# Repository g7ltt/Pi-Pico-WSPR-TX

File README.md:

# Pi-Pico-WSPR-TX
17M WSPR transmitter for the Pi Pico (other bands possible with filter changes)

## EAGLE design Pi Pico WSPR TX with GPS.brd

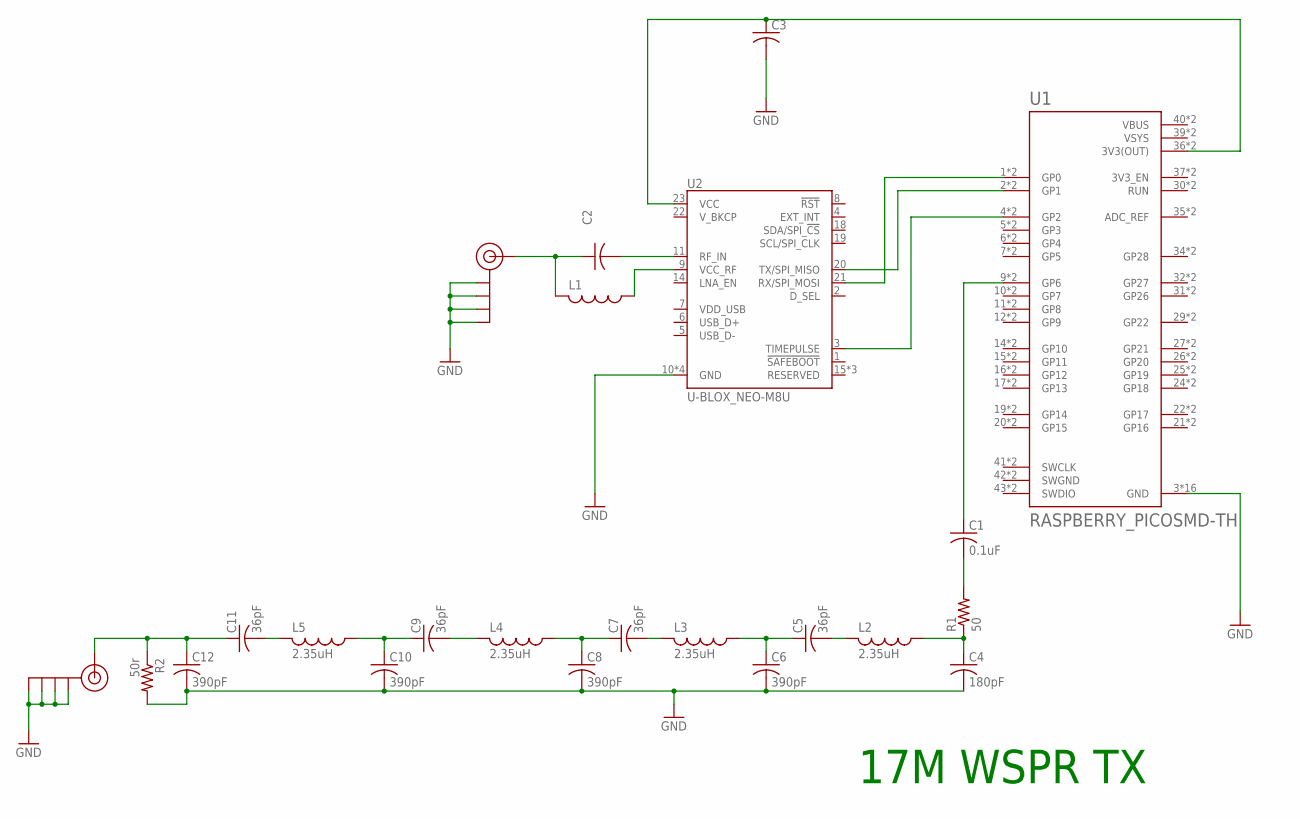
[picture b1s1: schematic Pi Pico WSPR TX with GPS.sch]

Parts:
C1: 0.1uF; C0603
C2, C3: C-USC0603; C0603
C4: 180pF; C0603
C5, C7, C9, C11: 36pF; C0603
C6, C8, C10, C12: 390pF; C0603
J$1, J$2: SMA_EDGE; SMA-EDGE
L1: L-USL2012C; L2012C
L2, L3, L4, L5: 2.35uH; L2012C
R1: 50; R0603
R2: 50r; R0603
U1: RASPBERRY_PICOSMD-TH; PICO-PKG
U2: U-BLOX_NEO-M8U; NEO-M9N/M8T/M8U/D9S/F9P

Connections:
GND: C3.2, C4.2, C6.2, C8.2, C10.2, C12.2, J$1.GND@0 (GND), J$1.GND@1 (GND), J$1.GND@2 (GND), J$1.GND@3 (GND), J$2.GND@0 (GND), J$2.GND@1 (GND), J$2.GND@2 (GND), J$2.GND@3 (GND), R2.2, U1.3 (GND), U1.8 (GND), U1.13 (GND), U1.18 (GND), U1.23 (GND), U1.28 (GND), U1.33 (GND), U1.38 (GND), U1.P$3 (GND), U1.P$8 (GND), U1.P$13 (GND), U1.P$18 (GND), U1.P$23 (GND), U1.P$28 (GND), U1.P$33 (GND), U1.P$38 (GND), U2.10 (GND), U2.12 (GND), U2.13 (GND), U2.24 (GND)
unnamed: C2.1, J$1.SIG (SIGNAL), L1.2
unnamed: C3.1, U1.36 (3V3(OUT)), U1.P$36 (3V3(OUT)), U2.23 (VCC)
unnamed: U1.4 (GP2), U1.P$4 (GP2), U2.3 (TIMEPULSE)
unnamed: C1.1, U1.9 (GP6), U1.P$9 (GP6)
unnamed: U1.1 (GP0), U1.P$1 (GP0), U2.21 (RX/SPI_MOSI)
unnamed: U1.2 (GP1), U1.P$2 (GP1), U2.20 (TX/SPI_MISO)
unnamed: C1.2, R1.2
unnamed: C2.2, U2.11 (RF_IN)
unnamed: L1.1, U2.9 (VCC_RF)
unnamed: C11.2, L5.2
unnamed: C4.1, L2.1, R1.1
unnamed: C5.2, L2.2
unnamed: C5.1, C6.1, L3.1
unnamed: C7.2, L3.2
unnamed: C7.1, C8.1, L4.1
unnamed: C9.2, L4.2
unnamed: C9.1, C10.1, L5.1
unnamed: C11.1, C12.1, J$2.SIG (SIGNAL), R2.1
SWGND: U1.42 (SWGND), U1.P$42 (SWGND)
VBUS: U1.40 (VBUS), U1.P$40 (VBUS)
VSYS: U1.39 (VSYS), U1.P$39 (VSYS)

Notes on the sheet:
17M WSPR TX

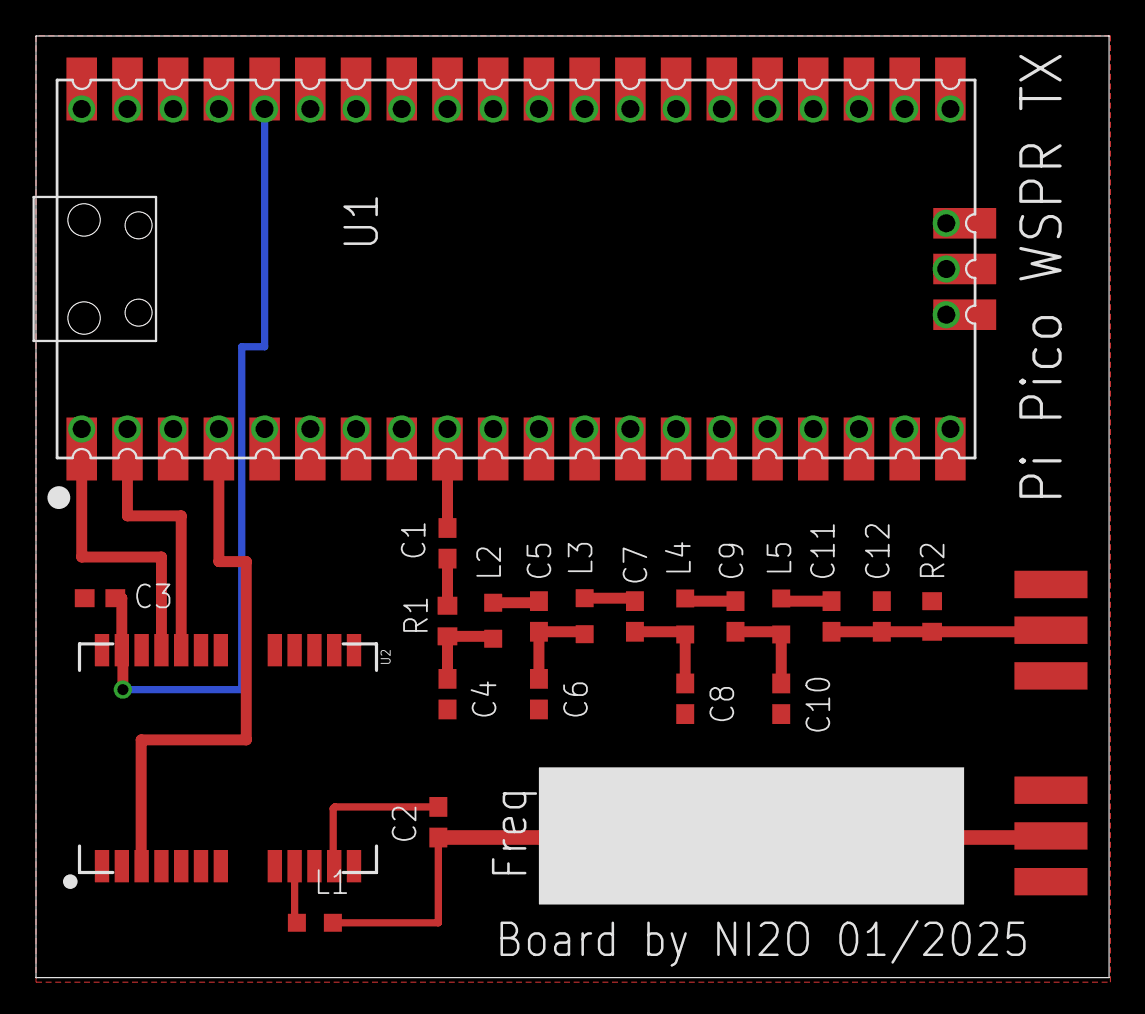
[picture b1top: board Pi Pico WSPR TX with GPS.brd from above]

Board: 2 copper layers, 59.6 x 52.3 mm, 23 parts (0 on the bottom side), 22 nets.

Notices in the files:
parts and their libraries:
SparkFun-Retired: Licensing: Creative Commons ShareAlike 4.0 International - https://creativecommons.org/licenses/by-sa/4.0
